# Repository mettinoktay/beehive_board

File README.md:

# beehive_board
An Atmega328 based board to control beehives remotely

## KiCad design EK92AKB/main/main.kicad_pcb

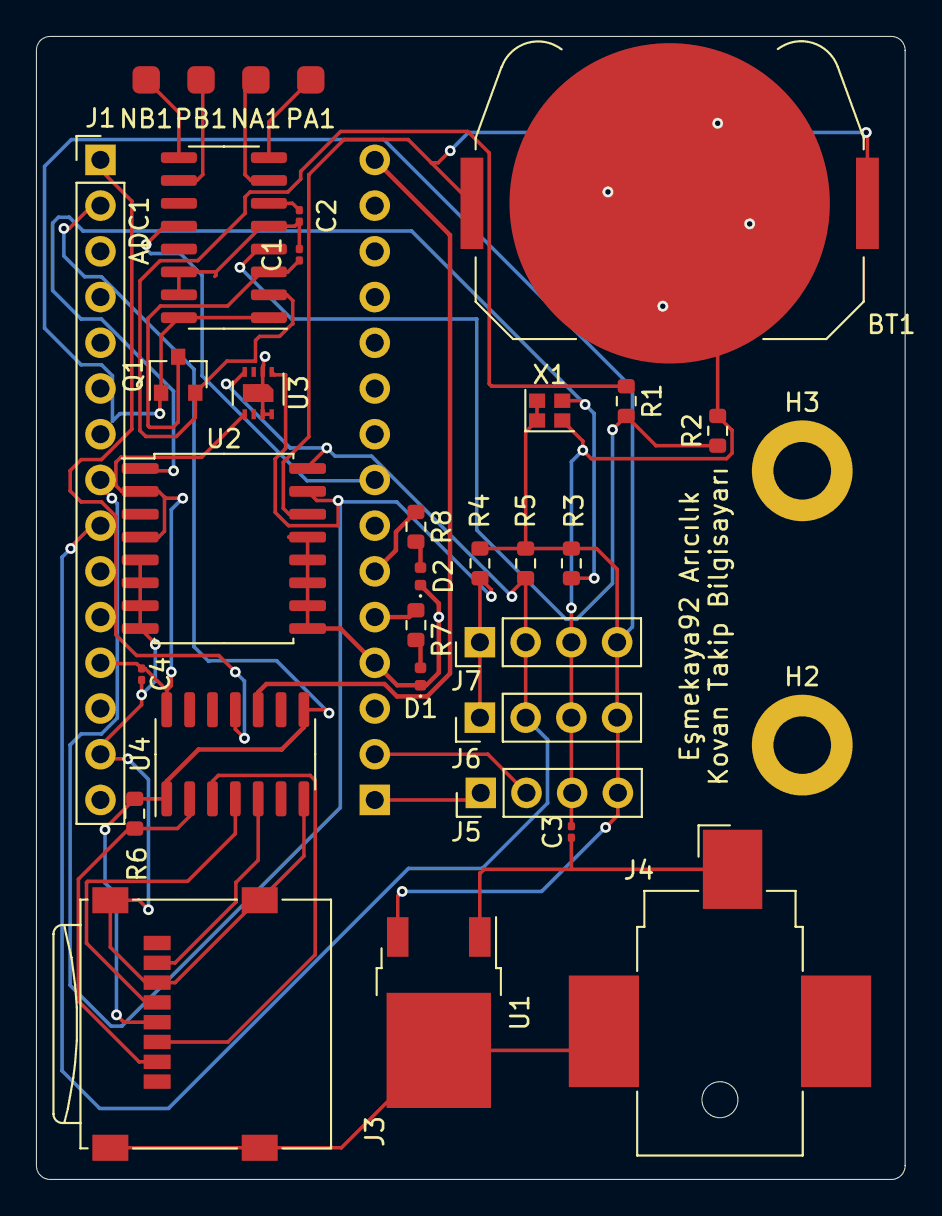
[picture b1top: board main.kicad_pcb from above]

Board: 2 copper layers, 48.3 x 63.5 mm, 35 parts (1 on the bottom side), 32 nets.

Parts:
ADC1: HX711; SOP-16_3.9x9.9mm_P1.27mm
BT1: Battery_Cell; BatteryHolder_Keystone_3034_1x20mm
C1: 10uF; C_0201_0603Metric
C2, C4: 0.1uF; C_0201_0603Metric
C3: 0.33uF; C_0201_0603Metric
D1, D2: LED; LED_0402_1005Metric
H2, H3: MountingHole; MountingHole_3.2mm_M3_DIN965_Pad
J1, J2: Conn_01x15_Male; PinHeader_1x15_P2.54mm_Vertical
J3: Micro_SD_Card; microSD_HC_Wuerth_693072010801
J4: Barrel_Jack; BarrelJack_CUI_PJ-036AH-SMT_Horizontal
J5, J6, J7: Conn_01x04; PinHeader_1x04_P2.54mm_Vertical
NA1: SOLDER_PAD; Solder_Pad
NB1: SOLDER_PAD; Solder_Pad
PA1: SOLDER_PAD; Solder_Pad
PB1: SOLDER_PAD; Solder_Pad
Q1: S8550; SOT-23
R1, R2: R_Small; R_0603_1608Metric
R3, R4, R5, R6: 10k; R_0603_1608Metric
R7, R8: 1K; R_0603_1608Metric
U1: L7805; TO-252-2
U2: DS3231M; SOIC-16W_7.5x10.3mm_P1.27mm
U3: SHT31-DIS; Sensirion_DFN-8-1EP_2.5x2.5mm_P0.5mm_EP1.1x1.7mm
U4: TXB0104D; SOIC-14_3.9x8.7mm_P1.27mm
X1: SG-3030CM; Crystal_SMD_2016-4Pin_2.0x1.6mm

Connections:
3V3: J1.2, J3.4, R6.1, U4.1, U4.8
5V: ADC1.1, ADC1.16, C4.1, J1.12, J5.4, J6.4, J7.4, Q1.1, R3.2, R4.1, R5.1, U1.3, U2.2, U2.4, U3.5, U4.14, X1.1, X1.4
D2_LED: J2.5, R7.1
D3_LED: J2.6, R8.1
D4_SCK: ADC1.11, J2.7
D5_DOUT: ADC1.12, J2.8
D10_CS: J2.13, U4.13
D11_DIN: J2.14, U4.12
D12_DOUT: J2.15, U4.10
D13_SCK: J1.1, U4.11
GND: ADC1.5, ADC1.14, ADC1.15, BT1.2, C1.2, C2.2, C3.2, C4.2, D1.1, D2.1, J1.14, J2.4, J3.6, J3.9, J4.2, J5.3, J6.3, J7.3, R2.2, U1.2, U2.5, U2.6, U2.7, U2.8, U2.9, U2.10, U2.11, U2.12, U2.13, U3.2, U3.7, U3.8, U3.9, U4.7, X1.2
unnamed: ADC1.2, Q1.2, R1.1
unnamed: ADC1.3, C1.1, Q1.3
unnamed: ADC1.4, R1.2, R2.1
unnamed: ADC1.6, C2.1
unnamed: ADC1.7, NA1.1
unnamed: ADC1.8, PA1.1
unnamed: ADC1.9, NB1.1
unnamed: ADC1.10, PB1.1
unnamed: BT1.1, U2.14
unnamed: C3.1, J4.1, U1.1
unnamed: D1.2, R7.2
unnamed: D2.2, R8.2
unnamed: R3.1, U2.1, X1.3
RX: J2.2, J5.2
SCL: J1.9, J6.2, J7.2, R5.2, U2.16, U3.4
SDA: J1.8, J6.1, J7.1, R4.2, U2.15, U3.1
SD_CS: J3.2, R6.2, U4.2
SD_DIN: J3.3, U4.3
SD_DOUT: J3.7, U4.5
SD_SCK: J3.5, U4.4
TX: J2.1, J5.1
